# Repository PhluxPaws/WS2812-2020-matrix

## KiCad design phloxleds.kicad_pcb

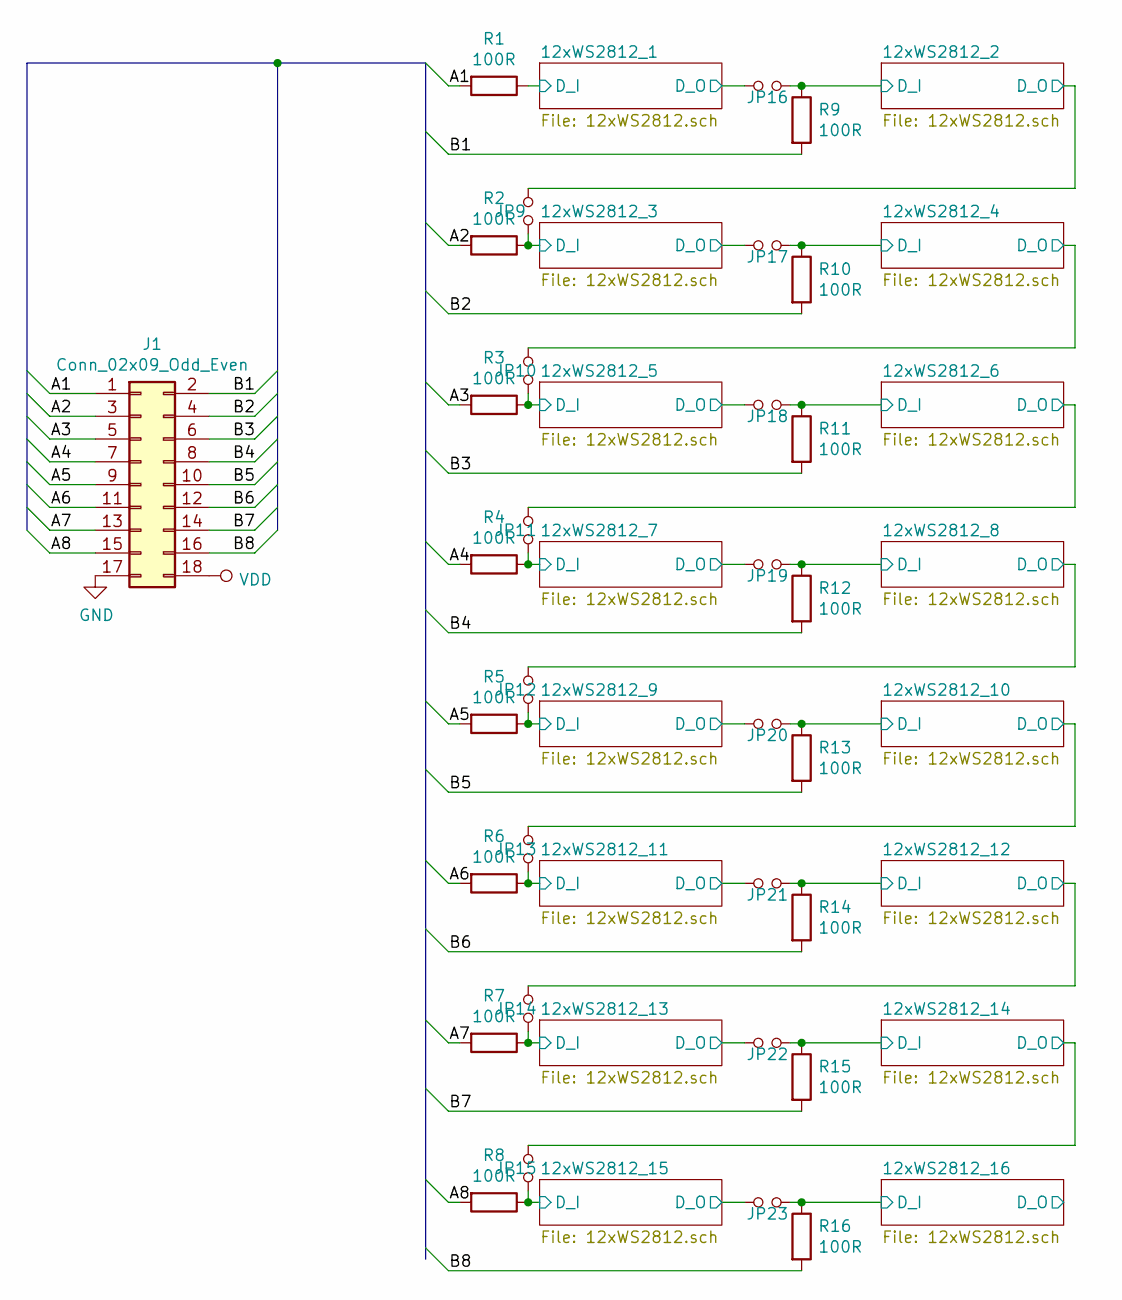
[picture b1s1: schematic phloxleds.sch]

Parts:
J1: Conn_02x09_Odd_Even; PinHeader_2x09_P2.54mm_Vertical
JP9, JP10, JP11, JP12, JP13, JP14, JP15, JP16, JP17, JP18, JP19, JP20, JP21, JP22, JP23: Jumper_NO_Small; SmolJumper
R1, R2, R3, R4, R5, R6, R7, R8, R9, R10, R11, R12, R13, R14, R15, R16: 100R; R_0603_1608Metric_Pad1.05x0.95mm_HandSolder

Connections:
/12xWS2812_1/D_I: R1.1; also elsewhere on the board
/12xWS2812_1/D_O: JP16.1; also elsewhere on the board
/12xWS2812_2/D_I: JP16.2, R9.1; also elsewhere on the board
/12xWS2812_2/D_O: JP9.1; also elsewhere on the board
/12xWS2812_3/D_I: JP9.2, R2.1; also elsewhere on the board
/12xWS2812_3/D_O: JP17.1; also elsewhere on the board
/12xWS2812_4/D_I: JP17.2, R10.1; also elsewhere on the board
/12xWS2812_4/D_O: JP10.1; also elsewhere on the board
/12xWS2812_5/D_I: JP10.2, R3.1; also elsewhere on the board
/12xWS2812_5/D_O: JP18.1; also elsewhere on the board
/12xWS2812_6/D_I: JP18.2, R11.1; also elsewhere on the board
/12xWS2812_6/D_O: JP11.1; also elsewhere on the board
/12xWS2812_7/D_I: JP11.2, R4.1; also elsewhere on the board
/12xWS2812_7/D_O: JP19.1; also elsewhere on the board
/12xWS2812_8/D_I: JP19.2, R12.1; also elsewhere on the board
/12xWS2812_8/D_O: JP12.1; also elsewhere on the board
/12xWS2812_9/D_I: JP12.2, R5.1; also elsewhere on the board
/12xWS2812_9/D_O: JP20.1; also elsewhere on the board
/12xWS2812_10/D_I: JP20.2, R13.1; also elsewhere on the board
/12xWS2812_10/D_O: JP13.1; also elsewhere on the board
/12xWS2812_11/D_I: JP13.2, R6.1; also elsewhere on the board
/12xWS2812_11/D_O: JP21.1; also elsewhere on the board
/12xWS2812_12/D_I: JP21.2, R14.1; also elsewhere on the board
/12xWS2812_12/D_O: JP14.1; also elsewhere on the board
/12xWS2812_13/D_I: JP14.2, R7.1; also elsewhere on the board
/12xWS2812_13/D_O: JP22.1; also elsewhere on the board
/12xWS2812_14/D_I: JP22.2, R15.1; also elsewhere on the board
/12xWS2812_14/D_O: JP15.1; also elsewhere on the board
/12xWS2812_15/D_I: JP15.2, R8.1; also elsewhere on the board
/12xWS2812_15/D_O: JP23.1; also elsewhere on the board
/12xWS2812_16/D_I: JP23.2, R16.1; also elsewhere on the board
/A1: J1.1, R1.2
/A2: J1.3, R2.2
/A3: J1.5, R3.2
/A4: J1.7, R4.2
/A5: J1.9, R5.2
/A6: J1.11, R6.2
/A7: J1.13, R7.2
/A8: J1.15, R8.2
/B1: J1.2, R9.2
/B2: J1.4, R10.2
/B3: J1.6, R11.2
/B4: J1.8, R12.2
/B5: J1.10, R13.2
/B6: J1.12, R14.2
/B7: J1.14, R15.2
/B8: J1.16, R16.2
GND: J1.17; also elsewhere on the board
VDD: J1.18; also elsewhere on the board

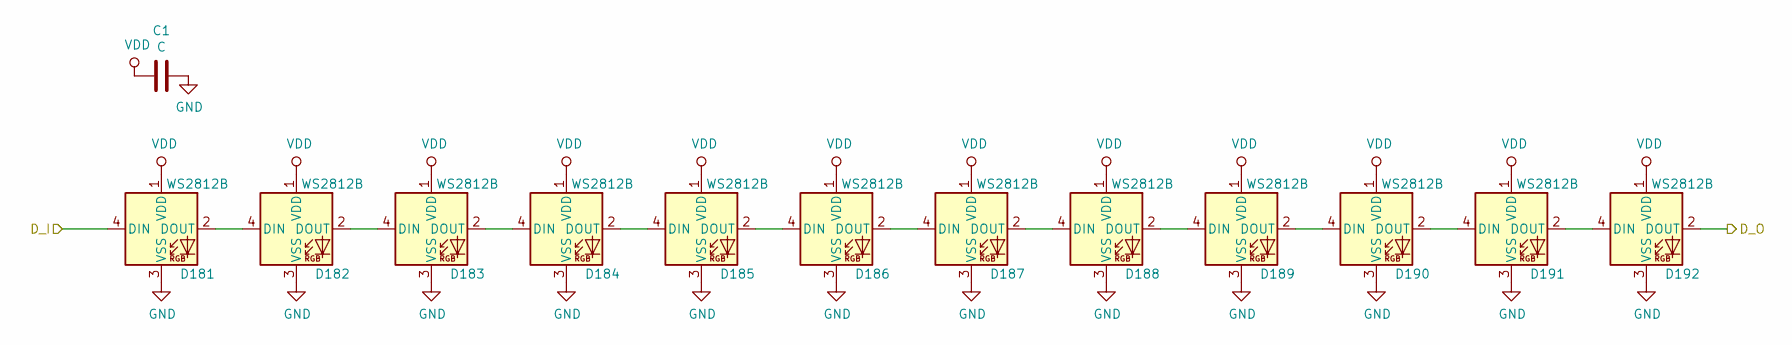
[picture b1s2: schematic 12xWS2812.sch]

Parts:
C1: C; C_0603_1608Metric
D181, D182, D183, D184, D185, D186, D187, D188, D189, D190, D191, D192: WS2812B; LED_WS2812B_2020

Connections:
/12xWS2812_1/D_I: D181.4 (DIN); also elsewhere on the board
/12xWS2812_1/D_O: D192.2 (DOUT); also elsewhere on the board
GND: C1.1, D181.3 (VSS), D182.3 (VSS), D183.3 (VSS), D184.3 (VSS), D185.3 (VSS), D186.3 (VSS), D187.3 (VSS), D188.3 (VSS), D189.3 (VSS), D190.3 (VSS), D191.3 (VSS), D192.3 (VSS); also elsewhere on the board
unnamed: D181.2 (DOUT), D182.4 (DIN)
unnamed: D182.2 (DOUT), D183.4 (DIN)
unnamed: D183.2 (DOUT), D184.4 (DIN)
unnamed: D184.2 (DOUT), D185.4 (DIN)
unnamed: D185.2 (DOUT), D186.4 (DIN)
unnamed: D186.2 (DOUT), D187.4 (DIN)
unnamed: D187.2 (DOUT), D188.4 (DIN)
unnamed: D188.2 (DOUT), D189.4 (DIN)
unnamed: D189.2 (DOUT), D190.4 (DIN)
unnamed: D190.2 (DOUT), D191.4 (DIN)
unnamed: D191.2 (DOUT), D192.4 (DIN)
VDD: C1.2, D181.1 (VDD), D182.1 (VDD), D183.1 (VDD), D184.1 (VDD), D185.1 (VDD), D186.1 (VDD), D187.1 (VDD), D188.1 (VDD), D189.1 (VDD), D190.1 (VDD), D191.1 (VDD), D192.1 (VDD); also elsewhere on the board

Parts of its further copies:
C2, C3, C4, C5, C6, C7, C8, C9, C10, C11, C12, C13, C14, C15, C16: C; C_0603_1608Metric
D1, D2, D3, D4, D5, D6, D7, D8, D9, D10, D11, D12, D13, D14, D15, D16, D17, D18, D19, D20, D21, D22, D23, D24, D25, D26, D27, D28, D29, D30, D31, D32, D33, D34, D35, D36, D37, D38, D39, D40, D41, D42, D43, D44, D45, D46, D47, D48, D49, D50, D51, D52, D53, D54, D55, D56, D57, D58, D59, D60, D61, D62, D63, D64, D65, D66, D67, D68, D69, D70, D71, D72, D73, D74, D75, D76, D77, D78, D79, D80, D81, D82, D83, D84, D85, D86, D87, D88, D89, D90, D91, D92, D93, D94, D95, D96, D97, D98, D99, D100, D101, D102, D103, D104, D105, D106, D107, D108, D109, D110, D111, D112, D113, D114, D115, D116, D117, D118, D119, D120, D121, D122, D123, D124, D125, D126, D127, D128, D129, D130, D131, D132, D133, D134, D135, D136, D137, D138, D139, D140, D141, D142, D143, D144, D145, D146, D147, D148, D149, D150, D151, D152, D153, D154, D155, D156, D157, D158, D159, D160, D161, D162, D163, D164, D165, D166, D167, D168, D169, D170, D171, D172, D173, D174, D175, D176, D177, D178, D179, D180: WS2812B; LED_WS2812B_2020

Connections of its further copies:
/12xWS2812_2/D_I: D169.4 (DIN); also elsewhere on the board
/12xWS2812_2/D_O: D180.2 (DOUT); also elsewhere on the board
/12xWS2812_3/D_I: D13.4 (DIN); also elsewhere on the board
/12xWS2812_3/D_O: D24.2 (DOUT); also elsewhere on the board
/12xWS2812_4/D_I: D1.4 (DIN); also elsewhere on the board
/12xWS2812_4/D_O: D12.2 (DOUT); also elsewhere on the board
/12xWS2812_5/D_I: D37.4 (DIN); also elsewhere on the board
/12xWS2812_5/D_O: D48.2 (DOUT); also elsewhere on the board
/12xWS2812_6/D_I: D25.4 (DIN); also elsewhere on the board
/12xWS2812_6/D_O: D36.2 (DOUT); also elsewhere on the board
/12xWS2812_7/D_I: D61.4 (DIN); also elsewhere on the board
/12xWS2812_7/D_O: D72.2 (DOUT); also elsewhere on the board
/12xWS2812_8/D_I: D49.4 (DIN); also elsewhere on the board
/12xWS2812_8/D_O: D60.2 (DOUT); also elsewhere on the board
/12xWS2812_9/D_I: D85.4 (DIN); also elsewhere on the board
/12xWS2812_9/D_O: D96.2 (DOUT); also elsewhere on the board
/12xWS2812_10/D_I: D73.4 (DIN); also elsewhere on the board
/12xWS2812_10/D_O: D84.2 (DOUT); also elsewhere on the board
/12xWS2812_11/D_I: D109.4 (DIN); also elsewhere on the board
/12xWS2812_11/D_O: D120.2 (DOUT); also elsewhere on the board
/12xWS2812_12/D_I: D97.4 (DIN); also elsewhere on the board
/12xWS2812_12/D_O: D108.2 (DOUT); also elsewhere on the board
/12xWS2812_13/D_I: D133.4 (DIN); also elsewhere on the board
/12xWS2812_13/D_O: D144.2 (DOUT); also elsewhere on the board
/12xWS2812_14/D_I: D121.4 (DIN); also elsewhere on the board
/12xWS2812_14/D_O: D132.2 (DOUT); also elsewhere on the board
/12xWS2812_15/D_I: D157.4 (DIN); also elsewhere on the board
/12xWS2812_15/D_O: D168.2 (DOUT); also elsewhere on the board
/12xWS2812_16/D_I: D145.4 (DIN); also elsewhere on the board
/12xWS2812_16/D_O: D156.2 (DOUT)
GND: C2.1, C3.1, C4.1, C5.1, C6.1, C7.1, C8.1, C9.1, C10.1, C11.1, C12.1, C13.1, C14.1, C15.1, C16.1, D1.3 (VSS), D2.3 (VSS), D3.3 (VSS), D4.3 (VSS), D5.3 (VSS), D6.3 (VSS), D7.3 (VSS), D8.3 (VSS), D9.3 (VSS), D10.3 (VSS), D11.3 (VSS), D12.3 (VSS), D13.3 (VSS), D14.3 (VSS), D15.3 (VSS), D16.3 (VSS), D17.3 (VSS), D18.3 (VSS), D19.3 (VSS), D20.3 (VSS), D21.3 (VSS), D22.3 (VSS), D23.3 (VSS), D24.3 (VSS), D25.3 (VSS), D26.3 (VSS), D27.3 (VSS), D28.3 (VSS), D29.3 (VSS), D30.3 (VSS), D31.3 (VSS), D32.3 (VSS), D33.3 (VSS), D34.3 (VSS), D35.3 (VSS), D36.3 (VSS), D37.3 (VSS), D38.3 (VSS), D39.3 (VSS), D40.3 (VSS), D41.3 (VSS), D42.3 (VSS), D43.3 (VSS), D44.3 (VSS), D45.3 (VSS), D46.3 (VSS), D47.3 (VSS), D48.3 (VSS), D49.3 (VSS), D50.3 (VSS), D51.3 (VSS), D52.3 (VSS), D53.3 (VSS), D54.3 (VSS), D55.3 (VSS), D56.3 (VSS), D57.3 (VSS), D58.3 (VSS), D59.3 (VSS), D60.3 (VSS), D61.3 (VSS), D62.3 (VSS), D63.3 (VSS), D64.3 (VSS), D65.3 (VSS), D66.3 (VSS), D67.3 (VSS), D68.3 (VSS), D69.3 (VSS), D70.3 (VSS), D71.3 (VSS), D72.3 (VSS), D73.3 (VSS), D74.3 (VSS), D75.3 (VSS), D76.3 (VSS), D77.3 (VSS), D78.3 (VSS), D79.3 (VSS), D80.3 (VSS), D81.3 (VSS), D82.3 (VSS), D83.3 (VSS), D84.3 (VSS), D85.3 (VSS), D86.3 (VSS), D87.3 (VSS), D88.3 (VSS), D89.3 (VSS), D90.3 (VSS), D91.3 (VSS), D92.3 (VSS), D93.3 (VSS), D94.3 (VSS), D95.3 (VSS), D96.3 (VSS), D97.3 (VSS), D98.3 (VSS), D99.3 (VSS), D100.3 (VSS), D101.3 (VSS), D102.3 (VSS), D103.3 (VSS), D104.3 (VSS), D105.3 (VSS), D106.3 (VSS), D107.3 (VSS), D108.3 (VSS), D109.3 (VSS), D110.3 (VSS), D111.3 (VSS), D112.3 (VSS), D113.3 (VSS), D114.3 (VSS), D115.3 (VSS), D116.3 (VSS), D117.3 (VSS), D118.3 (VSS), D119.3 (VSS), D120.3 (VSS), D121.3 (VSS), D122.3 (VSS), D123.3 (VSS), D124.3 (VSS), D125.3 (VSS), D126.3 (VSS), D127.3 (VSS), D128.3 (VSS), D129.3 (VSS), D130.3 (VSS), D131.3 (VSS), D132.3 (VSS), D133.3 (VSS), D134.3 (VSS), D135.3 (VSS), D136.3 (VSS), D137.3 (VSS), D138.3 (VSS), D139.3 (VSS), D140.3 (VSS), D141.3 (VSS), D142.3 (VSS), D143.3 (VSS), D144.3 (VSS), D145.3 (VSS), D146.3 (VSS), D147.3 (VSS), D148.3 (VSS), D149.3 (VSS), D150.3 (VSS), D151.3 (VSS), D152.3 (VSS), D153.3 (VSS), D154.3 (VSS), D155.3 (VSS), D156.3 (VSS), D157.3 (VSS), D158.3 (VSS), D159.3 (VSS), D160.3 (VSS), D161.3 (VSS), D162.3 (VSS), D163.3 (VSS), D164.3 (VSS), D165.3 (VSS), D166.3 (VSS), D167.3 (VSS), D168.3 (VSS), D169.3 (VSS), D170.3 (VSS), D171.3 (VSS), D172.3 (VSS), D173.3 (VSS), D174.3 (VSS), D175.3 (VSS), D176.3 (VSS), D177.3 (VSS), D178.3 (VSS), D179.3 (VSS), D180.3 (VSS); also elsewhere on the board
unnamed: D1.2 (DOUT), D2.4 (DIN)
unnamed: D2.2 (DOUT), D3.4 (DIN)
unnamed: D3.2 (DOUT), D4.4 (DIN)
unnamed: D4.2 (DOUT), D5.4 (DIN)
unnamed: D5.2 (DOUT), D6.4 (DIN)
unnamed: D6.2 (DOUT), D7.4 (DIN)
unnamed: D7.2 (DOUT), D8.4 (DIN)
unnamed: D8.2 (DOUT), D9.4 (DIN)
unnamed: D10.2 (DOUT), D11.4 (DIN)
unnamed: D9.2 (DOUT), D10.4 (DIN)
unnamed: D11.2 (DOUT), D12.4 (DIN)
unnamed: D13.2 (DOUT), D14.4 (DIN)
unnamed: D14.2 (DOUT), D15.4 (DIN)
unnamed: D15.2 (DOUT), D16.4 (DIN)
unnamed: D16.2 (DOUT), D17.4 (DIN)
unnamed: D17.2 (DOUT), D18.4 (DIN)
unnamed: D18.2 (DOUT), D19.4 (DIN)
unnamed: D19.2 (DOUT), D20.4 (DIN)
unnamed: D20.2 (DOUT), D21.4 (DIN)
unnamed: D21.2 (DOUT), D22.4 (DIN)
unnamed: D22.2 (DOUT), D23.4 (DIN)
unnamed: D23.2 (DOUT), D24.4 (DIN)
unnamed: D25.2 (DOUT), D26.4 (DIN)
unnamed: D26.2 (DOUT), D27.4 (DIN)
unnamed: D27.2 (DOUT), D28.4 (DIN)
unnamed: D28.2 (DOUT), D29.4 (DIN)
unnamed: D29.2 (DOUT), D30.4 (DIN)
unnamed: D30.2 (DOUT), D31.4 (DIN)
unnamed: D31.2 (DOUT), D32.4 (DIN)
unnamed: D32.2 (DOUT), D33.4 (DIN)
unnamed: D33.2 (DOUT), D34.4 (DIN)
unnamed: D34.2 (DOUT), D35.4 (DIN)
unnamed: D35.2 (DOUT), D36.4 (DIN)
unnamed: D37.2 (DOUT), D38.4 (DIN)
unnamed: D38.2 (DOUT), D39.4 (DIN)
unnamed: D39.2 (DOUT), D40.4 (DIN)
unnamed: D40.2 (DOUT), D41.4 (DIN)
unnamed: D41.2 (DOUT), D42.4 (DIN)
unnamed: D42.2 (DOUT), D43.4 (DIN)
unnamed: D43.2 (DOUT), D44.4 (DIN)
unnamed: D44.2 (DOUT), D45.4 (DIN)
unnamed: D45.2 (DOUT), D46.4 (DIN)
unnamed: D46.2 (DOUT), D47.4 (DIN)
unnamed: D47.2 (DOUT), D48.4 (DIN)
unnamed: D49.2 (DOUT), D50.4 (DIN)
unnamed: D50.2 (DOUT), D51.4 (DIN)
unnamed: D51.2 (DOUT), D52.4 (DIN)
unnamed: D52.2 (DOUT), D53.4 (DIN)
unnamed: D53.2 (DOUT), D54.4 (DIN)
unnamed: D54.2 (DOUT), D55.4 (DIN)
unnamed: D55.2 (DOUT), D56.4 (DIN)
unnamed: D56.2 (DOUT), D57.4 (DIN)
unnamed: D57.2 (DOUT), D58.4 (DIN)
unnamed: D58.2 (DOUT), D59.4 (DIN)
unnamed: D59.2 (DOUT), D60.4 (DIN)
unnamed: D61.2 (DOUT), D62.4 (DIN)
unnamed: D62.2 (DOUT), D63.4 (DIN)
unnamed: D63.2 (DOUT), D64.4 (DIN)
unnamed: D64.2 (DOUT), D65.4 (DIN)
unnamed: D65.2 (DOUT), D66.4 (DIN)
unnamed: D66.2 (DOUT), D67.4 (DIN)
unnamed: D67.2 (DOUT), D68.4 (DIN)
unnamed: D68.2 (DOUT), D69.4 (DIN)
unnamed: D69.2 (DOUT), D70.4 (DIN)
unnamed: D70.2 (DOUT), D71.4 (DIN)
unnamed: D71.2 (DOUT), D72.4 (DIN)
unnamed: D73.2 (DOUT), D74.4 (DIN)
unnamed: D74.2 (DOUT), D75.4 (DIN)
unnamed: D75.2 (DOUT), D76.4 (DIN)
unnamed: D76.2 (DOUT), D77.4 (DIN)
unnamed: D77.2 (DOUT), D78.4 (DIN)
unnamed: D78.2 (DOUT), D79.4 (DIN)
unnamed: D79.2 (DOUT), D80.4 (DIN)
unnamed: D80.2 (DOUT), D81.4 (DIN)
unnamed: D81.2 (DOUT), D82.4 (DIN)
unnamed: D82.2 (DOUT), D83.4 (DIN)
unnamed: D83.2 (DOUT), D84.4 (DIN)
unnamed: D85.2 (DOUT), D86.4 (DIN)
unnamed: D86.2 (DOUT), D87.4 (DIN)
unnamed: D87.2 (DOUT), D88.4 (DIN)
unnamed: D88.2 (DOUT), D89.4 (DIN)
unnamed: D89.2 (DOUT), D90.4 (DIN)
unnamed: D90.2 (DOUT), D91.4 (DIN)
unnamed: D91.2 (DOUT), D92.4 (DIN)
unnamed: D92.2 (DOUT), D93.4 (DIN)
unnamed: D93.2 (DOUT), D94.4 (DIN)
unnamed: D94.2 (DOUT), D95.4 (DIN)
unnamed: D95.2 (DOUT), D96.4 (DIN)
unnamed: D97.2 (DOUT), D98.4 (DIN)
unnamed: D98.2 (DOUT), D99.4 (DIN)
unnamed: D100.2 (DOUT), D101.4 (DIN)
unnamed: D99.2 (DOUT), D100.4 (DIN)
unnamed: D101.2 (DOUT), D102.4 (DIN)
unnamed: D102.2 (DOUT), D103.4 (DIN)
unnamed: D103.2 (DOUT), D104.4 (DIN)
unnamed: D104.2 (DOUT), D105.4 (DIN)
unnamed: D105.2 (DOUT), D106.4 (DIN)
unnamed: D106.2 (DOUT), D107.4 (DIN)
unnamed: D107.2 (DOUT), D108.4 (DIN)
unnamed: D109.2 (DOUT), D110.4 (DIN)
unnamed: D110.2 (DOUT), D111.4 (DIN)
unnamed: D111.2 (DOUT), D112.4 (DIN)
unnamed: D112.2 (DOUT), D113.4 (DIN)
unnamed: D113.2 (DOUT), D114.4 (DIN)
unnamed: D114.2 (DOUT), D115.4 (DIN)
unnamed: D115.2 (DOUT), D116.4 (DIN)
unnamed: D116.2 (DOUT), D117.4 (DIN)
unnamed: D117.2 (DOUT), D118.4 (DIN)
unnamed: D118.2 (DOUT), D119.4 (DIN)
unnamed: D119.2 (DOUT), D120.4 (DIN)
unnamed: D121.2 (DOUT), D122.4 (DIN)
unnamed: D122.2 (DOUT), D123.4 (DIN)
unnamed: D123.2 (DOUT), D124.4 (DIN)
unnamed: D124.2 (DOUT), D125.4 (DIN)
unnamed: D125.2 (DOUT), D126.4 (DIN)
unnamed: D126.2 (DOUT), D127.4 (DIN)
unnamed: D127.2 (DOUT), D128.4 (DIN)
unnamed: D128.2 (DOUT), D129.4 (DIN)
unnamed: D129.2 (DOUT), D130.4 (DIN)
unnamed: D130.2 (DOUT), D131.4 (DIN)
unnamed: D131.2 (DOUT), D132.4 (DIN)
unnamed: D133.2 (DOUT), D134.4 (DIN)
unnamed: D134.2 (DOUT), D135.4 (DIN)
unnamed: D135.2 (DOUT), D136.4 (DIN)
unnamed: D136.2 (DOUT), D137.4 (DIN)
unnamed: D137.2 (DOUT), D138.4 (DIN)
unnamed: D138.2 (DOUT), D139.4 (DIN)
unnamed: D139.2 (DOUT), D140.4 (DIN)
unnamed: D140.2 (DOUT), D141.4 (DIN)
unnamed: D141.2 (DOUT), D142.4 (DIN)
unnamed: D142.2 (DOUT), D143.4 (DIN)
unnamed: D143.2 (DOUT), D144.4 (DIN)
unnamed: D145.2 (DOUT), D146.4 (DIN)
unnamed: D146.2 (DOUT), D147.4 (DIN)
unnamed: D147.2 (DOUT), D148.4 (DIN)
unnamed: D148.2 (DOUT), D149.4 (DIN)
unnamed: D149.2 (DOUT), D150.4 (DIN)
unnamed: D150.2 (DOUT), D151.4 (DIN)
unnamed: D151.2 (DOUT), D152.4 (DIN)
unnamed: D152.2 (DOUT), D153.4 (DIN)
unnamed: D153.2 (DOUT), D154.4 (DIN)
unnamed: D154.2 (DOUT), D155.4 (DIN)
unnamed: D155.2 (DOUT), D156.4 (DIN)
unnamed: D157.2 (DOUT), D158.4 (DIN)
unnamed: D158.2 (DOUT), D159.4 (DIN)
unnamed: D159.2 (DOUT), D160.4 (DIN)
unnamed: D160.2 (DOUT), D161.4 (DIN)
unnamed: D161.2 (DOUT), D162.4 (DIN)
unnamed: D162.2 (DOUT), D163.4 (DIN)
unnamed: D163.2 (DOUT), D164.4 (DIN)
unnamed: D164.2 (DOUT), D165.4 (DIN)
unnamed: D165.2 (DOUT), D166.4 (DIN)
unnamed: D166.2 (DOUT), D167.4 (DIN)
unnamed: D167.2 (DOUT), D168.4 (DIN)
unnamed: D169.2 (DOUT), D170.4 (DIN)
unnamed: D170.2 (DOUT), D171.4 (DIN)
unnamed: D171.2 (DOUT), D172.4 (DIN)
unnamed: D172.2 (DOUT), D173.4 (DIN)
unnamed: D173.2 (DOUT), D174.4 (DIN)
unnamed: D174.2 (DOUT), D175.4 (DIN)
unnamed: D175.2 (DOUT), D176.4 (DIN)
unnamed: D176.2 (DOUT), D177.4 (DIN)
unnamed: D177.2 (DOUT), D178.4 (DIN)
unnamed: D178.2 (DOUT), D179.4 (DIN)
unnamed: D179.2 (DOUT), D180.4 (DIN)
VDD: C2.2, C3.2, C4.2, C5.2, C6.2, C7.2, C8.2, C9.2, C10.2, C11.2, C12.2, C13.2, C14.2, C15.2, C16.2, D1.1 (VDD), D2.1 (VDD), D3.1 (VDD), D4.1 (VDD), D5.1 (VDD), D6.1 (VDD), D7.1 (VDD), D8.1 (VDD), D9.1 (VDD), D10.1 (VDD), D11.1 (VDD), D12.1 (VDD), D13.1 (VDD), D14.1 (VDD), D15.1 (VDD), D16.1 (VDD), D17.1 (VDD), D18.1 (VDD), D19.1 (VDD), D20.1 (VDD), D21.1 (VDD), D22.1 (VDD), D23.1 (VDD), D24.1 (VDD), D25.1 (VDD), D26.1 (VDD), D27.1 (VDD), D28.1 (VDD), D29.1 (VDD), D30.1 (VDD), D31.1 (VDD), D32.1 (VDD), D33.1 (VDD), D34.1 (VDD), D35.1 (VDD), D36.1 (VDD), D37.1 (VDD), D38.1 (VDD), D39.1 (VDD), D40.1 (VDD), D41.1 (VDD), D42.1 (VDD), D43.1 (VDD), D44.1 (VDD), D45.1 (VDD), D46.1 (VDD), D47.1 (VDD), D48.1 (VDD), D49.1 (VDD), D50.1 (VDD), D51.1 (VDD), D52.1 (VDD), D53.1 (VDD), D54.1 (VDD), D55.1 (VDD), D56.1 (VDD), D57.1 (VDD), D58.1 (VDD), D59.1 (VDD), D60.1 (VDD), D61.1 (VDD), D62.1 (VDD), D63.1 (VDD), D64.1 (VDD), D65.1 (VDD), D66.1 (VDD), D67.1 (VDD), D68.1 (VDD), D69.1 (VDD), D70.1 (VDD), D71.1 (VDD), D72.1 (VDD), D73.1 (VDD), D74.1 (VDD), D75.1 (VDD), D76.1 (VDD), D77.1 (VDD), D78.1 (VDD), D79.1 (VDD), D80.1 (VDD), D81.1 (VDD), D82.1 (VDD), D83.1 (VDD), D84.1 (VDD), D85.1 (VDD), D86.1 (VDD), D87.1 (VDD), D88.1 (VDD), D89.1 (VDD), D90.1 (VDD), D91.1 (VDD), D92.1 (VDD), D93.1 (VDD), D94.1 (VDD), D95.1 (VDD), D96.1 (VDD), D97.1 (VDD), D98.1 (VDD), D99.1 (VDD), D100.1 (VDD), D101.1 (VDD), D102.1 (VDD), D103.1 (VDD), D104.1 (VDD), D105.1 (VDD), D106.1 (VDD), D107.1 (VDD), D108.1 (VDD), D109.1 (VDD), D110.1 (VDD), D111.1 (VDD), D112.1 (VDD), D113.1 (VDD), D114.1 (VDD), D115.1 (VDD), D116.1 (VDD), D117.1 (VDD), D118.1 (VDD), D119.1 (VDD), D120.1 (VDD), D121.1 (VDD), D122.1 (VDD), D123.1 (VDD), D124.1 (VDD), D125.1 (VDD), D126.1 (VDD), D127.1 (VDD), D128.1 (VDD), D129.1 (VDD), D130.1 (VDD), D131.1 (VDD), D132.1 (VDD), D133.1 (VDD), D134.1 (VDD), D135.1 (VDD), D136.1 (VDD), D137.1 (VDD), D138.1 (VDD), D139.1 (VDD), D140.1 (VDD), D141.1 (VDD), D142.1 (VDD), D143.1 (VDD), D144.1 (VDD), D145.1 (VDD), D146.1 (VDD), D147.1 (VDD), D148.1 (VDD), D149.1 (VDD), D150.1 (VDD), D151.1 (VDD), D152.1 (VDD), D153.1 (VDD), D154.1 (VDD), D155.1 (VDD), D156.1 (VDD), D157.1 (VDD), D158.1 (VDD), D159.1 (VDD), D160.1 (VDD), D161.1 (VDD), D162.1 (VDD), D163.1 (VDD), D164.1 (VDD), D165.1 (VDD), D166.1 (VDD), D167.1 (VDD), D168.1 (VDD), D169.1 (VDD), D170.1 (VDD), D171.1 (VDD), D172.1 (VDD), D173.1 (VDD), D174.1 (VDD), D175.1 (VDD), D176.1 (VDD), D177.1 (VDD), D178.1 (VDD), D179.1 (VDD), D180.1 (VDD); also elsewhere on the board

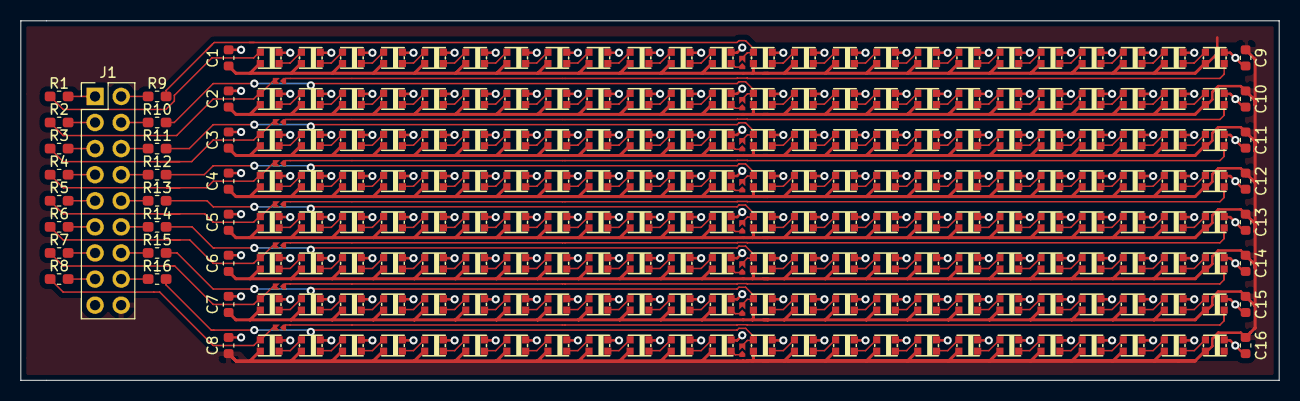
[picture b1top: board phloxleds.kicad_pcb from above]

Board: 2 copper layers, 122.5 x 35.0 mm, 240 parts (0 on the bottom side), 225 nets.
